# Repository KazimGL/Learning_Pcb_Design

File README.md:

# Learning PCB Design

A KiCad PCB design project created while following tutorials by **Ampnics**.

## 📌 Project Overview
- **Design Tool:** KiCad 8 / 10
- **Status:** Completed practice layout
- **Learning Source:** Inspired by / learned from [Ampnics YouTube Channel](https://www.youtube.com/@ampnics)

## 🖼️ Preview

## 📁 Repository Contents
- `Pcb_Design.kicad_sch` - Schematic File
- `Pcb_Design.kicad_pcb` - Board Layout File
- `Schemetic.pdf` - Printable Schematic
- `external components/` - Custom Footprints & Symbols

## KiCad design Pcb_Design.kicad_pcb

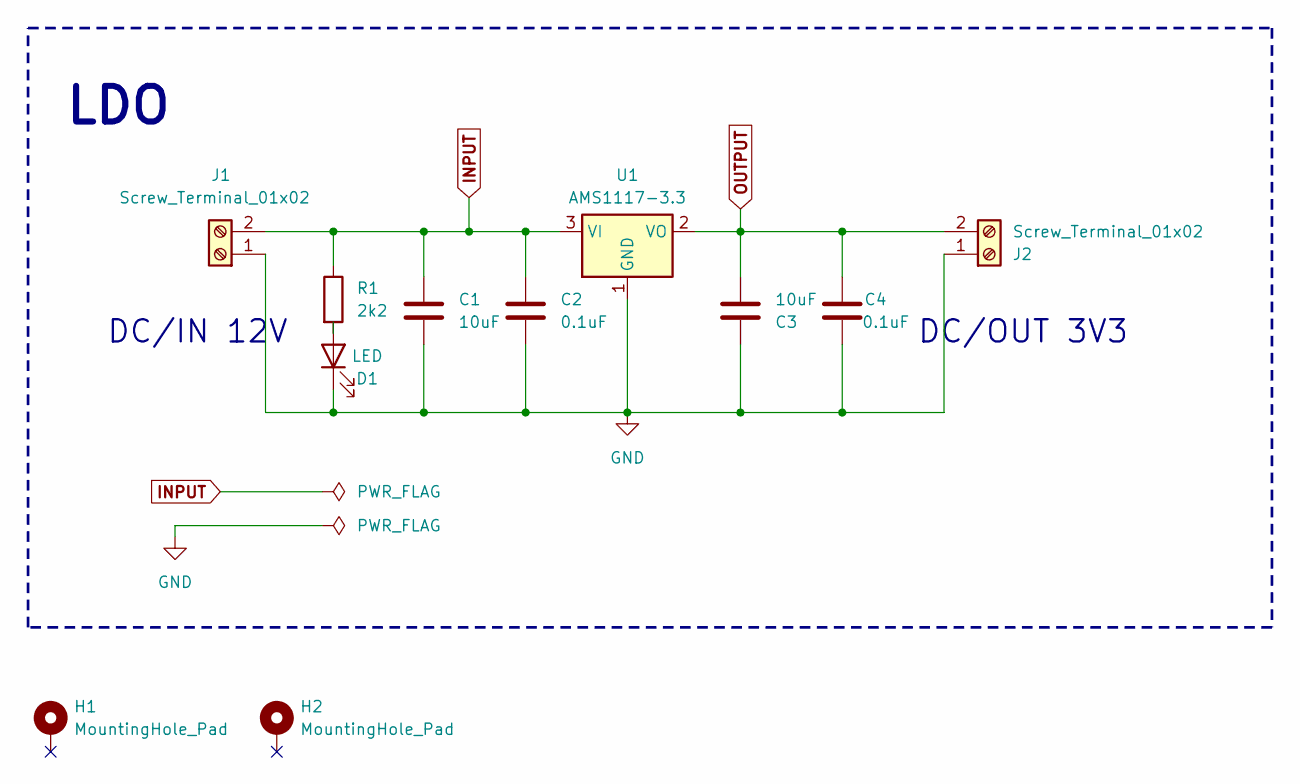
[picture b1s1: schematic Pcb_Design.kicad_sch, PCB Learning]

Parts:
C1, C3: 10uF; C_1206_3216Metric
C2, C4: 0.1uF; C_0603_1608Metric
D1: LED; LED_1206_3216Metric
H1, H2: MountingHole_Pad; MountingHole_2.2mm_M2_Pad_Via
J1, J2: Screw_Terminal_01x02; TerminalBlock_MaiXu_MX126-5.0-02P_1x02_P5.00mm
R1: 2k2; R_1206_3216Metric
U1: AMS1117-3.3; SOT-223-3_TabPin2

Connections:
GND: C1.2, C2.2, C3.1, C4.2, D1.1 (K), J1.1, J2.1, U1.1 (GND)
INPUT: C1.1, C2.1, J1.2, R1.1, U1.3 (VI)
unnamed: D1.2 (A), R1.2
OUTPUT: C3.2, C4.1, J2.2, U1.2 (VO)

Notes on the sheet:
DC/OUT 3V3
LDO
DC/IN 12V

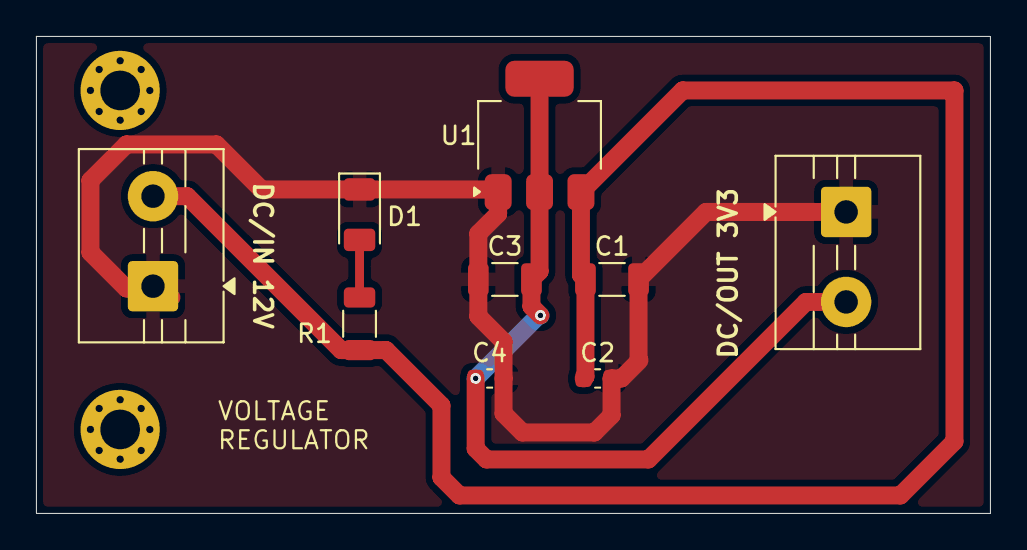
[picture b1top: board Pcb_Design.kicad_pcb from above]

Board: 2 copper layers, 53.0 x 26.5 mm, 11 parts (0 on the bottom side), 4 nets.
